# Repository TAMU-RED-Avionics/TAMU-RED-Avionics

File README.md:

# TAMU RED Avionics and Controls

This repository is home to the code and documentation for the Avionics and Controls subteam of the Texas A&M University Rocket Engine Design (<a href="https://www.tamured.space/">TAMU RED</a>) team.

## Organization

This repository is organized at the highest level by campaign. The current testing campaign is Elysium and all current code-related projects are found within. All previous campaigns are located within the Archive directory.

This repository is managed by <a href="https://github.com/Jacob-Hocevar">Jacob Hocevar</a>.

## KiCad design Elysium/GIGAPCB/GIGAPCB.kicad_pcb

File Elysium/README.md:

# Elysium
## Elysium GUI
The Elysium Graphical User Interface is the primary way that the system is controlled. It handels the inputs of the operator, automated control sequences, as well as the live display, graphing, and storage of data. It is programmed in C++ with Qt. For information on how to run and recompile (as needed), see the README.md in that directory.

## Real_Teensy
This directory contains the sketch(es) used by the Teensy to interpret the signals from the GUI, directly send the signals to actuate the valves, and read/transmit data from the sensors. Additionally, the system will handle an abort if there is a communications failure.

## Virtual_Teensy
This directory contains the code for a simulated version of the Teensy which is used to test the GUI. It recognizes and prints out any commands it recieves, and allows a user to control the data that it outputs to the GUI. For information on how to run and recompile (as needed), see the README.md in that directory.

Additionally, it will be configured to connect to another real Teensy to allow for Hardware In-the-Loop (HIL) testing.

## Data Formatting
For Elysium, all data will be transferred in `key:value` pairs. These pairs can be chained together in a comma separated string `"key1:val1,key2:val2,key3:val3\r\n"`, which terminates the carriage return (`'\r'`) and newline (`'\n'`) characters (the standard ending protocol for serial communication).The three goals are standardization, ease of maintainence/extension, and redundancy.

Standardization is both across programs and across subteams. We shall use the IDs of Sensors and Valves from the cross-team P&ID as the `key` terms, and the relevant data as the `value` terms. This will eliminate confusion between groups that were experienced in the WTS campaign, when one team was using `P1` and `P2`, and the other was using `PA` and `PB`.

This makes maintainence easier because it allows sensors and valves to be universally configured with a single, critical value. Similarly, if more valves or sensors are added, they can be added to the system with the same, single value.

This allows for some redundancy in the data transmission. If one value or part of a value fails to send correctly, the rest of the data in that batch (because of the keys), can still be readily and accurately identified by the receiver.

### Comparison to Older Design
Compare to the simpler system used during the WTS campaign: Comma separated values where the position dictates which property it corresponds to. First, the order of the properties had to be explicitly coordinated between the Teensy group and the GUI group and was not in reference to an existing, agreed upon document (such as the P&ID). Second, if a new sensor was added, both sides had to again determine where in the sequence to put the new value and manually hard-code it. Finally, if one value fails to send, all the following values (in that batch) are shifted and thus misread by the system.

### Example
Suppose the P&ID has three Pressure Transduces (P1-P3), two Thermocouples (T1 and T2) and one accelerometer (A1), which reads accelerations in three directions. The Teensy also outputs the local time with key `t`. Thus, it should output something like:

`"t:6545450000,P1:685.5422001,P2:14.78512405,P3:500.12124541,T1:7.2301502,T2:312.128575954,A1x:0.784213850,A1y:0.34517850652,A1z:2.0006781249\r\n"`

The order of the pairs does not matter, so something like the following is also acceptable, though less readable for debugging:

`"P3:500.12124541,A1x:0.784213850,P1:685.5422001,T2:312.128575954,A1z:2.0006781249,P2:14.78512405,T1:7.2301502,t:6545450000,A1y:0.34517850652\r\n"`

### Valve Example
For the valves, the solution is nearly identical, except that each command is always sent on its own line (no comma separated strings). Additionally, the value `0` always denotes a closed valve or close operation, and the value `1` always denotes an open valve or operation. For any extra electrical components (such as the ignition system), `0` will correspond to no power and `1` will correspond to providing power.

Consider a system with four normally closed solenoid valves (NCS1-NCS4) and two linearly-actuated ball valves (LA-BV 1 and LA-BV 2), and an igniter (IG1).

The signals to close all solenoids, open all ball valves and power igniter #1 would be given by:

`"NCS1:0\r\n"`
`"NCS2:0\r\n"`
`"NCS3:0\r\n"`
`"NCS4:0\r\n"`
`"LA-BV 1:1\r\n"`
`"LA-BV 2:1\r\n"`
`"IG1:1\r\n"`

Spaces in the IDs do not affect anything in either system. Again, these could be given in any order.

## Known Issues
There are a couple issues which have evaded all attempts to remove, but have simple methods to circumvent.

### GUI Freezes when connecting to Teensy
Identify: This typically results in the GUI freezing for several seconds, then expanding to full size, but not detecting any data inbound. It also will freeze upon shutdown or disconnect.

Cause: The connection to the Teensy is really sensitive with repeated connections and disconnections, especially with the WSL forwarding.

Solution: Unplug/replug the Teensy, and immediately attach it to WSL and attempt the connection again.<br>
A similar fix is to detach from WSL, and open the serial monitor in the Arduino IDE. Try opening and closing the serial monitor menu, and it should alternate between correct functionality, and a blank screen. When it is on a blank screen, close it, attach to WSL and attempt the connection again.

### GUI Connects, but the Teensy stays in the aborted state
Identify: GUI immediately "connects", but all data fields remain blank and the terminal is filled with `Not enough data: Aborted` and `Not enough data: New Input= nop`.

Cause: The connection to the Teensy is really sensitive and the first data sent over the connection often is lost/corrupted (buffer overriden?). This only occurs the first time after the Teensy is restarted.

Solution: Close the GUI and relaunch it. Not totally sure why, but it only ever happens the first time.

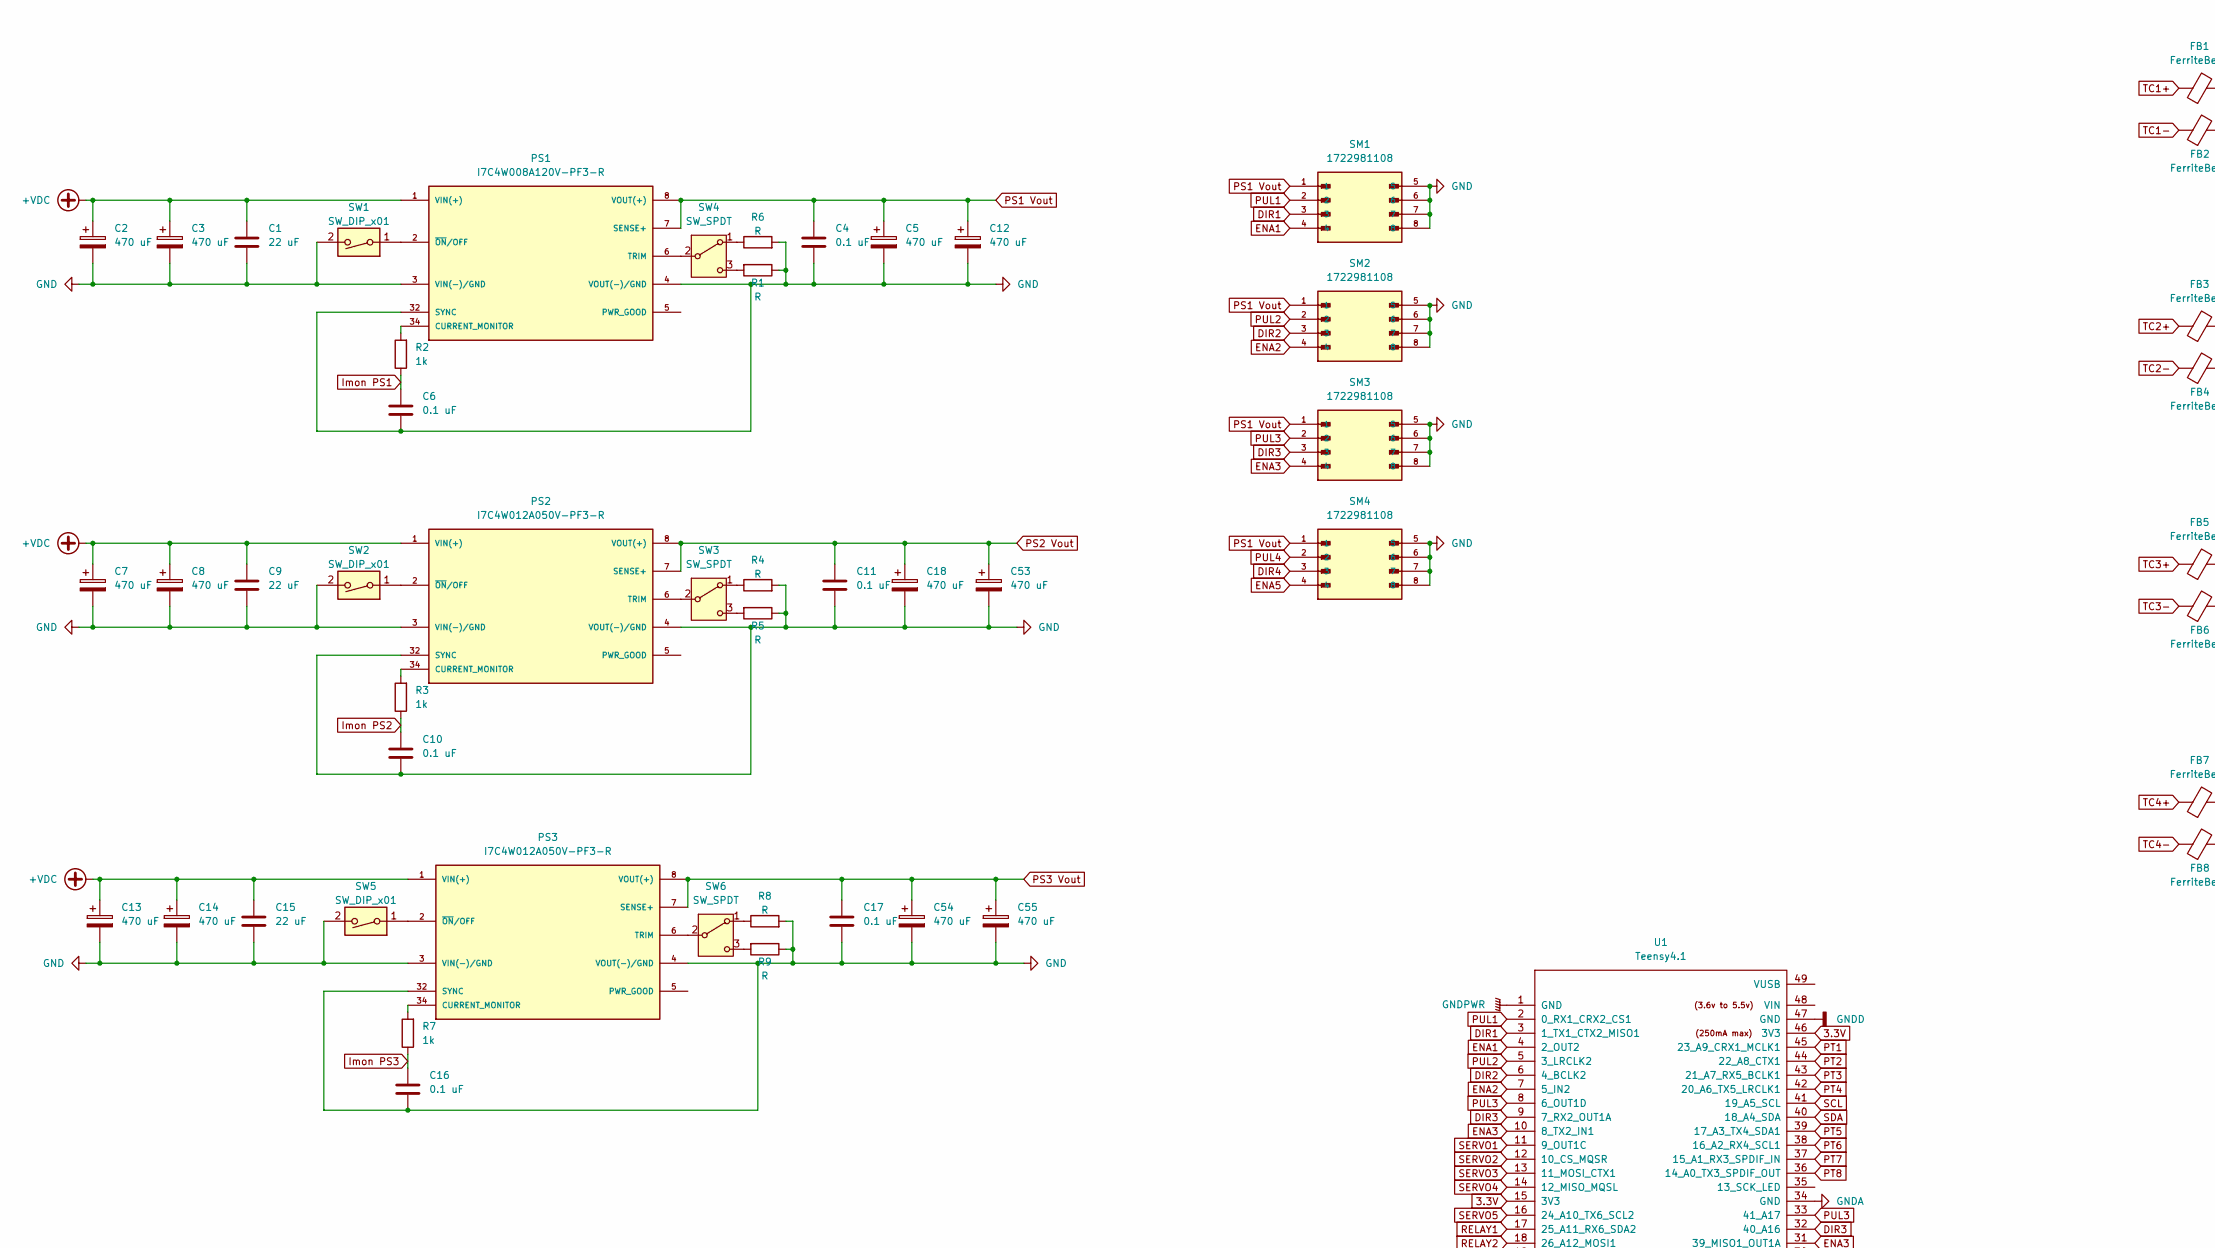
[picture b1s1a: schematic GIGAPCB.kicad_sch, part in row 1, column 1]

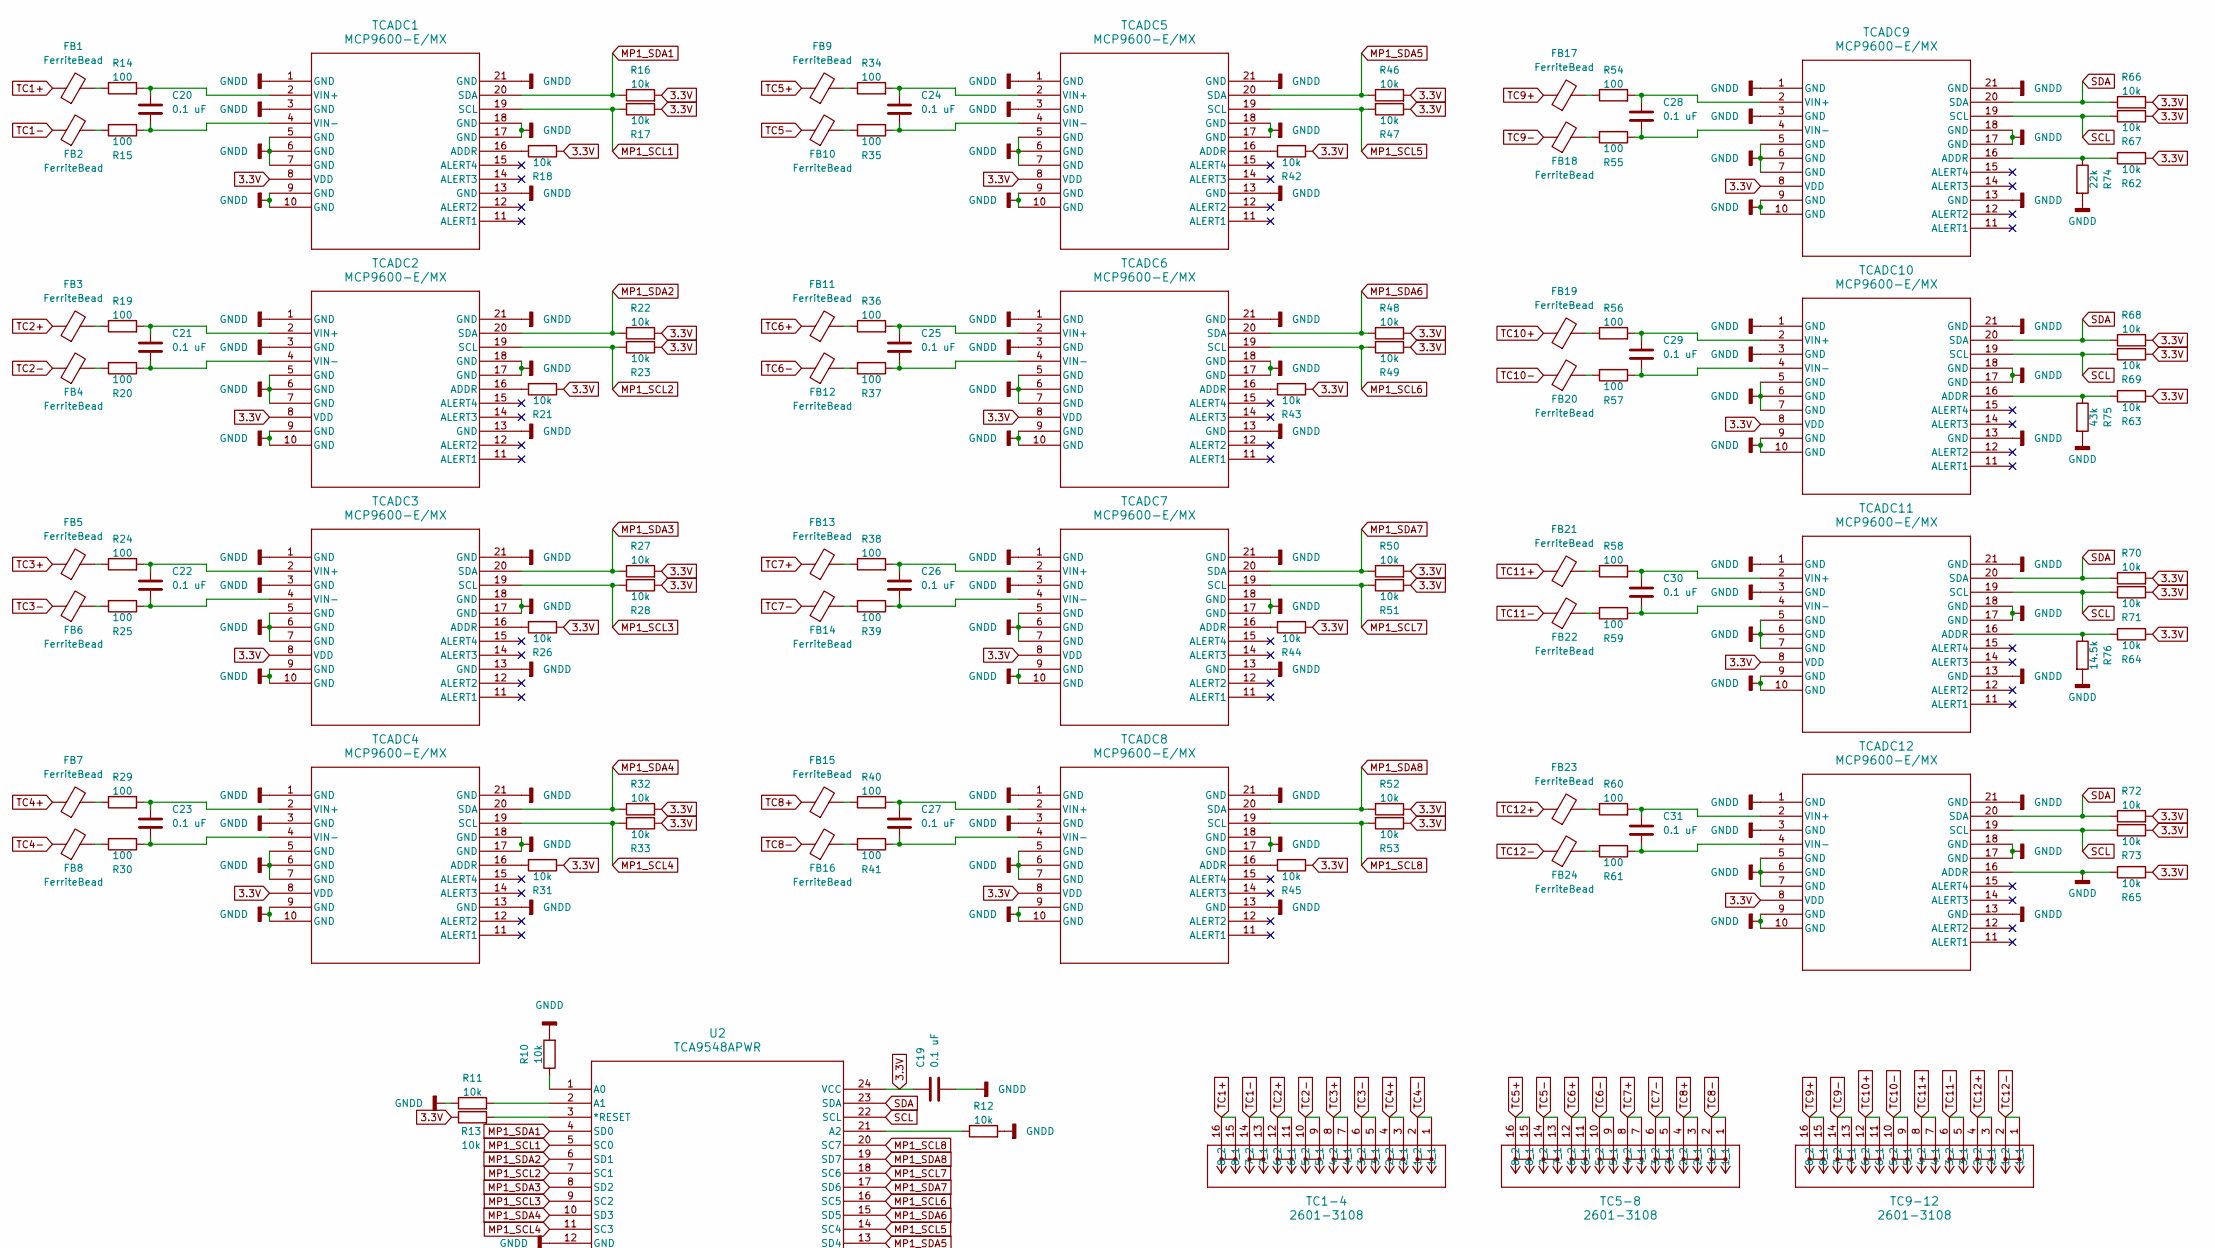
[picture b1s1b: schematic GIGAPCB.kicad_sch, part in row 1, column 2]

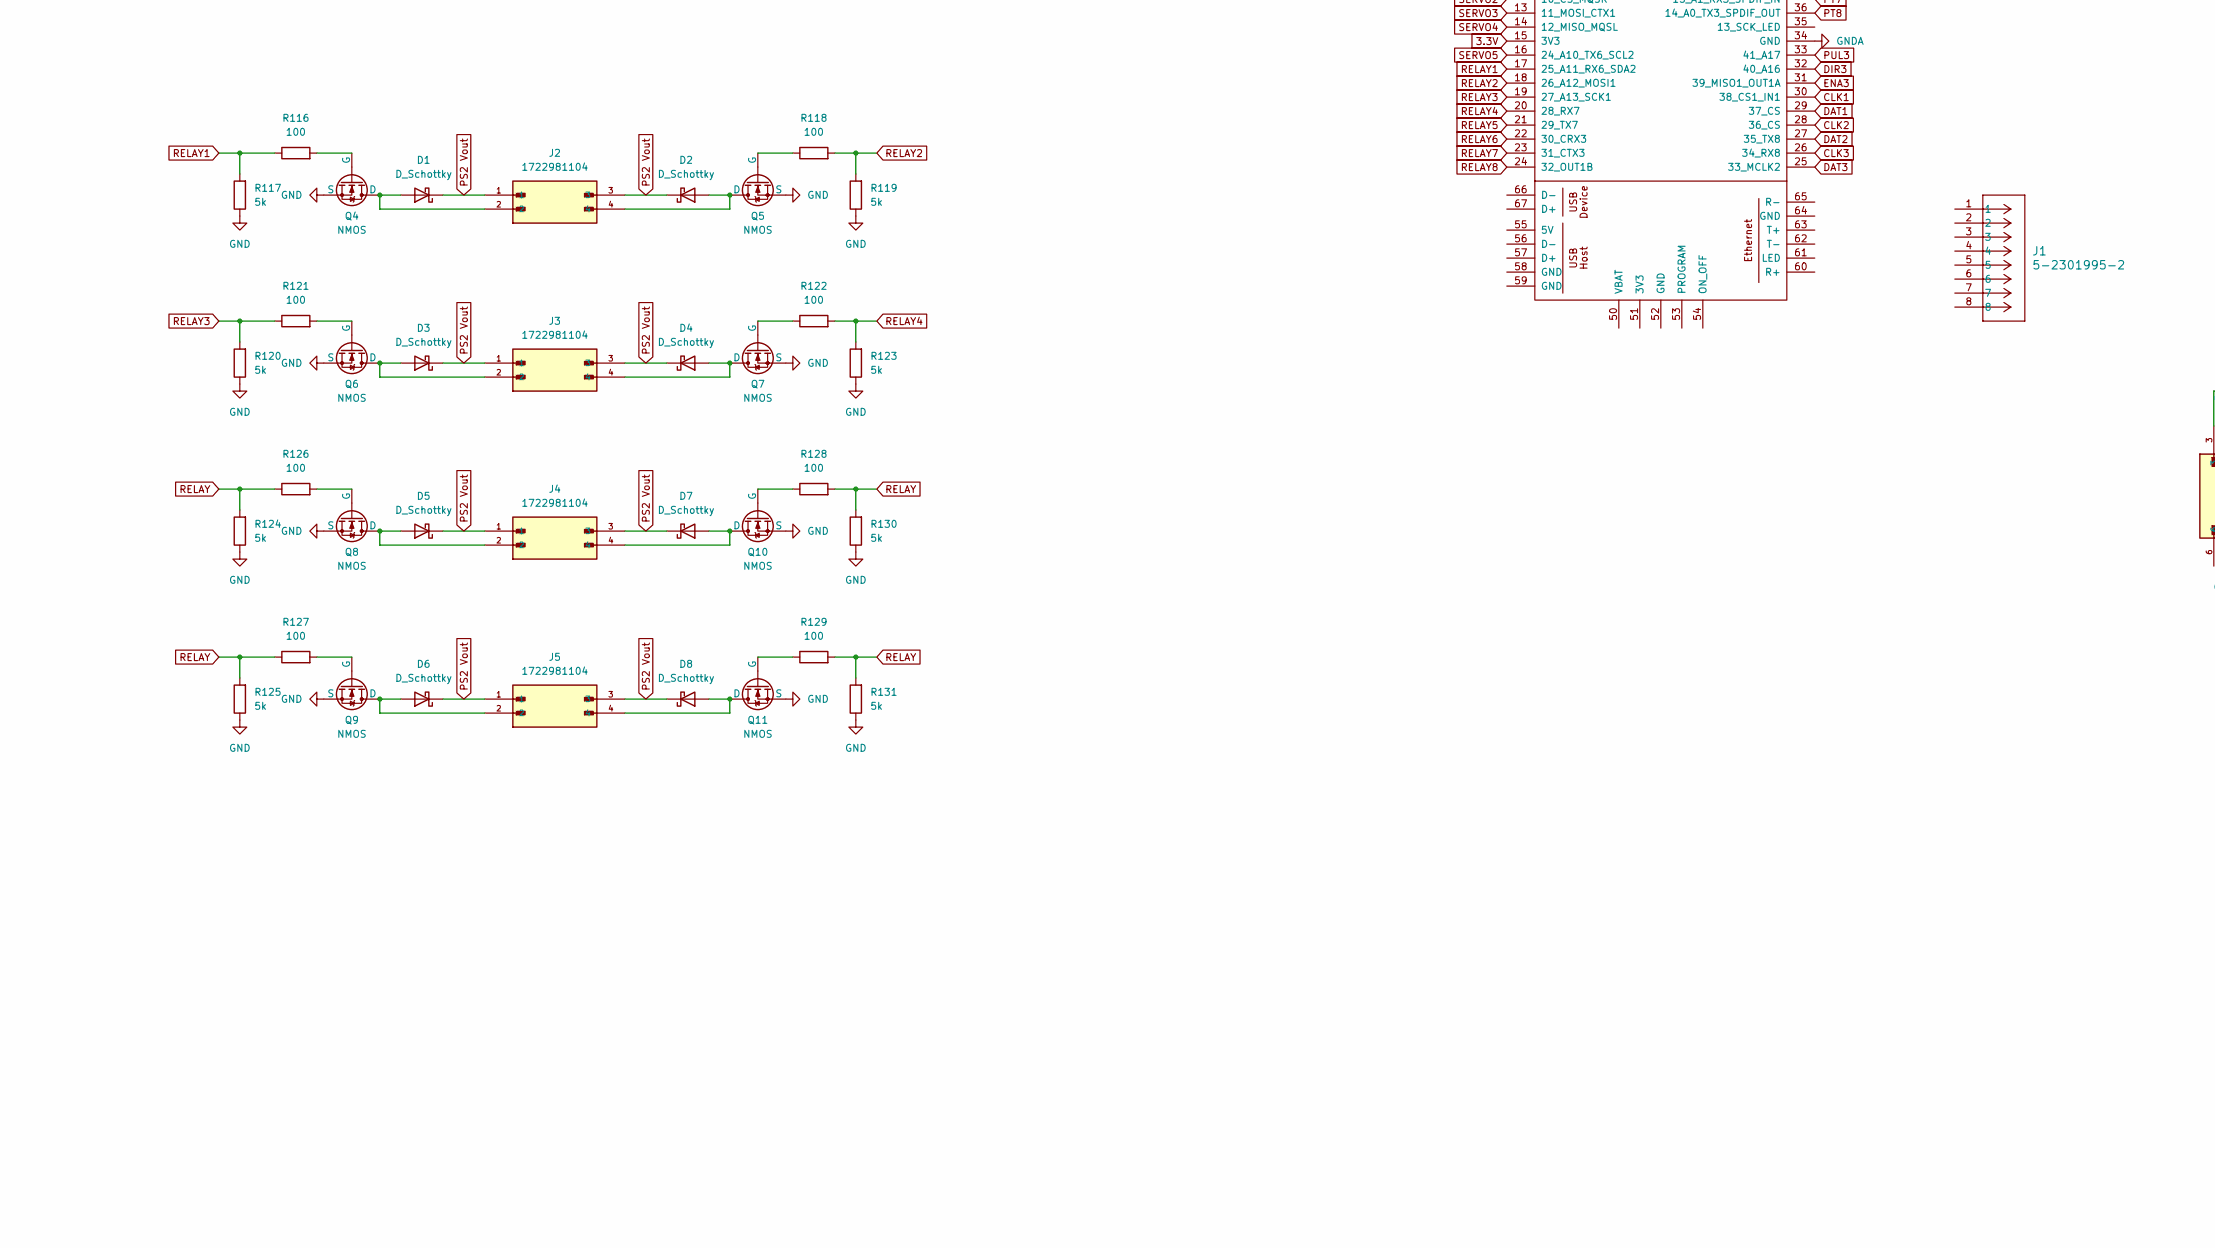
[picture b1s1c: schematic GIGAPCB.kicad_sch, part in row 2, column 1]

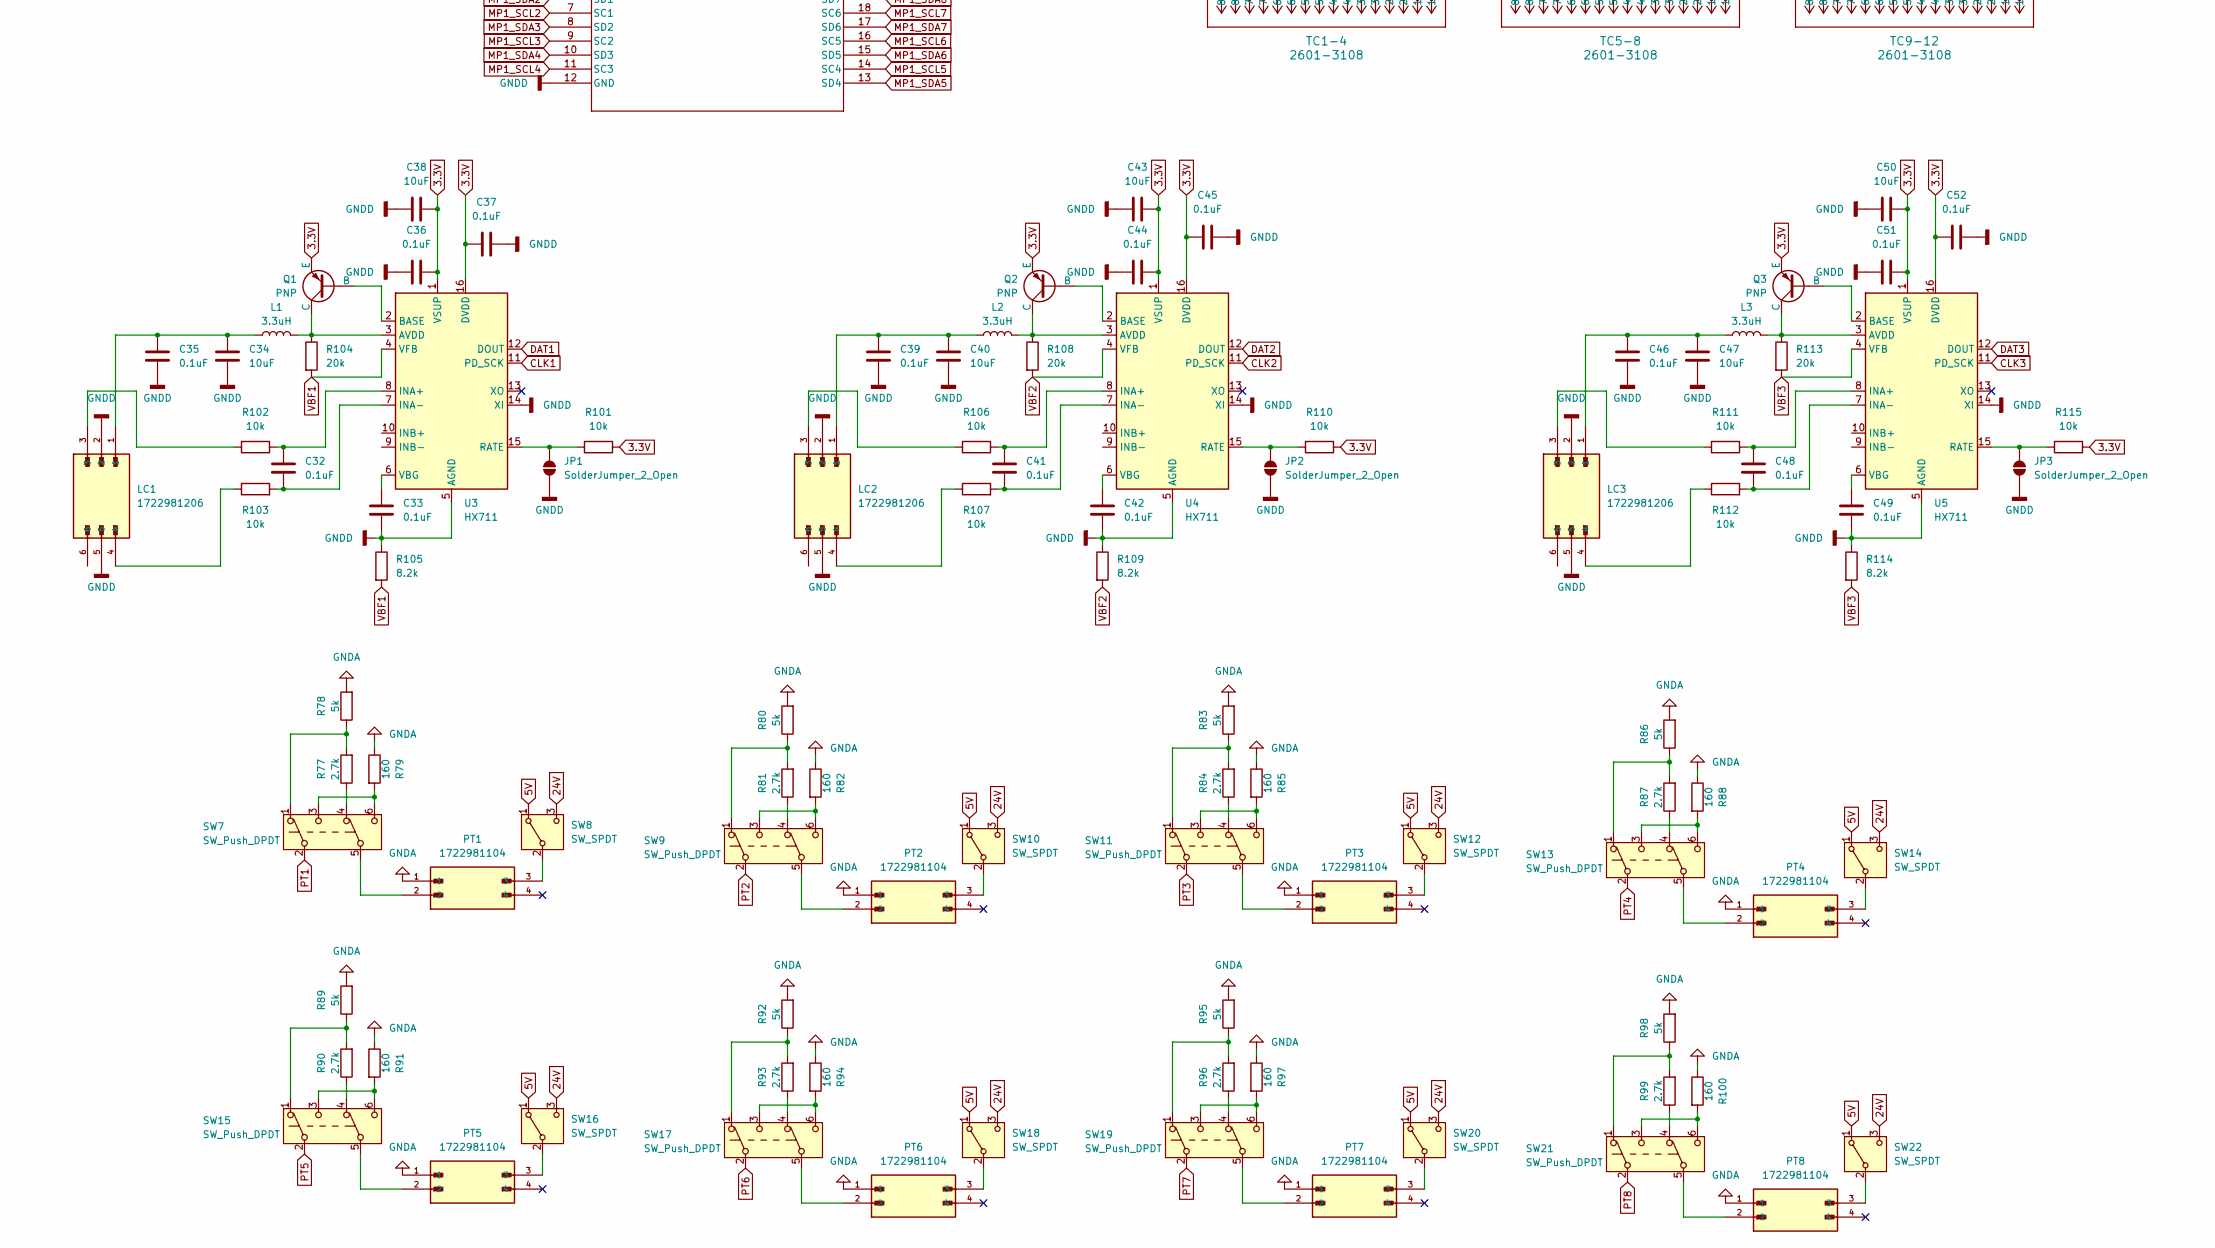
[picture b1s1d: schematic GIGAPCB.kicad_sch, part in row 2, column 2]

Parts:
C1, C9, C15: 22 uF; C_KRM55WR72A226MH01L
C2, C3, C5, C7, C8, C12, C13, C14, C18, C53, C54, C55: 470 uF; CP_EGPA101ELL471ML35S
C4, C6, C10, C11, C16, C17, C19, C20, C21, C22, C23, C24, C25, C26, C27, C28, C29, C30, C31: 0.1 uF; C_0805_2012Metric
C32, C33, C35, C36, C37, C39, C41, C42, C44, C45, C46, C48, C49, C51, C52: 0.1uF; C_0805_2012Metric
C34, C38, C40, C43, C47, C50: 10uF; C_1206_3216Metric
D1, D2, D3, D4, D5, D6, D7, D8: D_Schottky; D_PDS760_13-M
FB1, FB2, FB3, FB4, FB5, FB6, FB7, FB8, FB9, FB10, FB11, FB12, FB13, FB14, FB15, FB16, FB17, FB18, FB19, FB20, FB21, FB22, FB23, FB24: FerriteBead; R_0805_2012Metric
J1: 5-2301995-2; RJ25_Wayconn_MJEA-660X1_Horizontal
J2, J3, J4, J5: 1722981104; CONN_1722981104; PARTREV C1
JP1, JP2, JP3: SolderJumper_2_Open; SolderJumper-2_P1.3mm_Bridged2Bar_Pad1.0x1.5mm
L1, L2, L3: 3.3uH; C_0805_2012Metric
LC1, LC2, LC3: 1722981206; CONN_1722981106; PARTREV C1
PS1: I7C4W008A120V-PF3-R; DCC_I7C4W012A050V_PF3_R; PARTREV V5
PS2, PS3: I7C4W012A050V-PF3-R; DCC_I7C4W012A050V_PF3_R; PARTREV V5
PT1, PT2, PT3, PT4, PT5, PT6, PT7, PT8: 1722981104; CONN_1722981104; PARTREV C1
Q1: PNP; PinSocket_1x03_P2.54mm_Vertical
Q2, Q3: PNP
Q4, Q5, Q6, Q7, Q8, Q9, Q10, Q11: NMOS; MOSFET_CSD17306Q5A
R1, R4, R5, R6, R8, R9: R
R2, R3, R7: 1k
R10, R11, R12, R13, R16, R17, R18, R21, R22, R23, R26, R27, R28, R31, R32, R33, R42, R43, R44, R45, R46, R47, R48, R49, R50, R51, R52, R53, R62, R63, R64, R65, R66, R67, R68, R69, R70, R71, R72, R73, R101, R102, R103, R106, R107, R110, R111, R112, R115: 10k; R_0805_2012Metric
R14, R15, R19, R20, R24, R25, R29, R30, R34, R35, R36, R37, R38, R39, R40, R41, R54, R55, R56, R57, R58, R59, R60, R61, R116, R118, R121, R122, R126, R127, R128, R129: 100; R_0805_2012Metric
R74: 22k; R_0805_2012Metric
R75: 43k; R_0805_2012Metric
R76: 14.5k; R_0805_2012Metric
R77, R81, R84, R87, R90, R93, R96, R99: 2.7k; R_1206_3216Metric
R78, R80, R83, R86, R89, R92, R95, R98, R117, R119, R120, R123, R124, R125, R130, R131: 5k; R_1206_3216Metric
R79, R82, R85, R88, R91, R94, R97, R100: 160; R_1206_3216Metric
R104, R108, R113: 20k; R_0805_2012Metric
R105, R109, R114: 8.2k; R_0805_2012Metric
SM1, SM2, SM3, SM4: 1722981108; CONN_1722981108; PARTREV C1; DigiKey_Part_Number WM11582-ND
SW1, SW2, SW5: SW_DIP_x01
SW3, SW4, SW6, SW8, SW10, SW12, SW14, SW16, SW18, SW20, SW22: SW_SPDT; PinSocket_1x03_P2.54mm_Vertical
SW7, SW9, SW11, SW13, SW15, SW17, SW19, SW21: SW_Push_DPDT
TC1-4, TC5-8, TC9-12: 2601-3108; CONN_2601_3108
TCADC1, TCADC2, TCADC3, TCADC4, TCADC5, TCADC6, TCADC7, TCADC8, TCADC9, TCADC10, TCADC11, TCADC12: MCP9600-E/MX; IC_MCP9600-EMX-M
U1: Teensy4.1; Teensy41
U2: TCA9548APWR; IC_TCA9548APWR-M
U3, U4, U5: HX711; SOP-16_3.9x9.9mm_P1.27mm

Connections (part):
3.3V: C19.1, C36.2, C37.1, C38.2, C43.2, C44.2, C45.1, C50.2, C51.2, C52.1, Q1.3 (E), Q2.3 (E), Q3.3 (E), R13.1, R16.2, R17.1, R18.1, R21.1, R22.2, R23.1, R26.1, R27.2, R28.1, R31.1, R32.2, R33.1, R42.1, R43.1, R44.1, R45.1, R46.2, R47.1, R48.2, R49.1, R50.2, R51.1, R52.2, R53.1, R62.1, R63.1, R64.1, R65.1, R66.2, R67.1, R68.2, R69.1, R70.2, R71.1, R72.2, R73.1, R101.1, R110.1, R115.1, TCADC1.8 (VDD), TCADC2.8 (VDD), TCADC3.8 (VDD), TCADC4.8 (VDD), TCADC5.8 (VDD), TCADC6.8 (VDD), TCADC7.8 (VDD), TCADC8.8 (VDD), TCADC9.8 (VDD), TCADC10.8 (VDD), TCADC11.8 (VDD), TCADC12.8 (VDD), U1.15 (3V3), U1.46 (3V3), U2.24 (VCC), U3.1 (VSUP), U3.16 (DVDD), U4.1 (VSUP), U4.16 (DVDD), U5.1 (VSUP), U5.16 (DVDD)
5V: SW8.1 (A), SW10.1 (A), SW12.1 (A), SW14.1 (A), SW16.1 (A), SW18.1 (A), SW20.1 (A), SW22.1 (A)
24V: SW8.3 (C), SW10.3 (C), SW12.3 (C), SW14.3 (C), SW16.3 (C), SW18.3 (C), SW20.3 (C), SW22.3 (C)
+VDC: C1.1, C2.1, C3.1, C7.1, C8.1, C9.1, C13.1, C14.1, C15.1, PS1.1 (VIN(+)), PS2.1 (VIN(+)), PS3.1 (VIN(+))
CLK1: U1.30 (38_CS1_IN1), U3.11 (PD_SCK)
CLK2: U1.28 (36_CS), U4.11 (PD_SCK)
CLK3: U1.26 (34_RX8), U5.11 (PD_SCK)
DAT1: U1.29 (37_CS), U3.12 (DOUT)
DAT2: U1.27 (35_TX8), U4.12 (DOUT)
DAT3: U1.25 (33_MCLK2), U5.12 (DOUT)
DIR1: SM1.3, U1.3 (1_TX1_CTX2_MISO1)
DIR2: SM2.3, U1.6 (4_BCLK2)
DIR3: SM3.3, U1.9 (7_RX2_OUT1A), U1.32 (40_A16)
DIR4: SM4.3
ENA1: SM1.4, U1.4 (2_OUT2)
ENA2: SM2.4, U1.7 (5_IN2)
ENA3: SM3.4, U1.10 (8_TX2_IN1), U1.31 (39_MISO1_OUT1A)
ENA5: SM4.4
GND: C1.2, C2.2, C3.2, C4.2, C5.2, C6.2, C7.2, C8.2, C9.2, C10.2, C11.2, C12.2, C13.2, C14.2, C15.2, C16.2, C17.2, C18.2, C53.2, C54.2, C55.2, PS1.3 (VIN(-)/GND), PS1.4 (VOUT(-)/GND), PS1.32 (SYNC), PS2.3 (VIN(-)/GND), PS2.4 (VOUT(-)/GND), PS2.32 (SYNC), PS3.3 (VIN(-)/GND), PS3.4 (VOUT(-)/GND), PS3.32 (SYNC), Q4.3 (S), Q5.3 (S), Q6.3 (S), Q7.3 (S), Q8.3 (S), Q9.3 (S), Q10.3 (S), Q11.3 (S), R1.1, R4.2, R5.1, R6.2, R8.2, R9.1, R117.1, R119.1, R120.1, R123.1, R124.1, R125.1, R130.1, R131.1, SM1.5, SM1.6, SM1.7, SM1.8, SM2.5, SM2.6, SM2.7, SM2.8, SM3.5, SM3.6, SM3.7, SM3.8, SM4.5, SM4.6, SM4.7, SM4.8, SW1.2, SW2.2, SW5.2
GNDA: PT1.1, PT2.1, PT3.1, PT4.1, PT5.1, PT6.1, PT7.1, PT8.1, R78.2, R79.1, R80.2, R82.1, R83.2, R85.1, R86.2, R88.1, R89.2, R91.1, R92.2, R94.1, R95.2, R97.1, R98.2, R100.1, U1.34 (GND)
GNDD: C19.2, C33.2, C34.2, C35.2, C36.1, C37.2, C38.1, C39.2, C40.2, C42.2, C43.1, C44.1, C45.2, C46.2, C47.2, C49.2, C50.1, C51.1, C52.2, JP1.1 (A), JP2.1 (A), JP3.1 (A), LC1.2, LC1.5, LC2.2, LC2.5, LC3.2, LC3.5, R10.2, R11.1, R12.2, R65.2, R74.2, R75.2, R76.2, R105.1, R109.1, R114.1, TCADC1.1 (GND), TCADC1.3 (GND), TCADC1.5 (GND), TCADC1.6 (GND), TCADC1.7 (GND), TCADC1.9 (GND), TCADC1.10 (GND), TCADC1.13 (GND), TCADC1.17 (GND), TCADC1.18 (GND), TCADC1.21 (GND), TCADC2.1 (GND), TCADC2.3 (GND), TCADC2.5 (GND), TCADC2.6 (GND), TCADC2.7 (GND), TCADC2.9 (GND), TCADC2.10 (GND), TCADC2.13 (GND), TCADC2.17 (GND), TCADC2.18 (GND), TCADC2.21 (GND), TCADC3.1 (GND), TCADC3.3 (GND), TCADC3.5 (GND), TCADC3.6 (GND), TCADC3.7 (GND), TCADC3.9 (GND), TCADC3.10 (GND), TCADC3.13 (GND), TCADC3.17 (GND), TCADC3.18 (GND), TCADC3.21 (GND), TCADC4.1 (GND), TCADC4.3 (GND), TCADC4.5 (GND), TCADC4.6 (GND), TCADC4.7 (GND), TCADC4.9 (GND), TCADC4.10 (GND), TCADC4.13 (GND), TCADC4.17 (GND), TCADC4.18 (GND)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
GNDPWR: U1.1 (GND)
Imon PS1: C6.1, R2.1
Imon PS2: C10.1, R3.1
Imon PS3: C16.1, R7.1
MP1_SCL1: R17.2, TCADC1.19 (SCL), U2.5 (SC0)
MP1_SCL2: R23.2, TCADC2.19 (SCL), U2.7 (SC1)
MP1_SCL3: R28.2, TCADC3.19 (SCL), U2.9 (SC2)
MP1_SCL4: R33.2, TCADC4.19 (SCL), U2.11 (SC3)
MP1_SCL5: R47.2, TCADC5.19 (SCL), U2.14 (SC4)
MP1_SCL6: R49.2, TCADC6.19 (SCL), U2.16 (SC5)
MP1_SCL7: R51.2, TCADC7.19 (SCL), U2.18 (SC6)
MP1_SCL8: R53.2, TCADC8.19 (SCL), U2.20 (SC7)
MP1_SDA1: R16.1, TCADC1.20 (SDA), U2.4 (SD0)
MP1_SDA2: R22.1, TCADC2.20 (SDA), U2.6 (SD1)
MP1_SDA3: R27.1, TCADC3.20 (SDA), U2.8 (SD2)
MP1_SDA4: R32.1, TCADC4.20 (SDA), U2.10 (SD3)
MP1_SDA5: R46.1, TCADC5.20 (SDA), U2.13 (SD4)
MP1_SDA6: R48.1, TCADC6.20 (SDA), U2.15 (SD5)
MP1_SDA7: R50.1, TCADC7.20 (SDA), U2.17 (SD6)
MP1_SDA8: R52.1, TCADC8.20 (SDA), U2.19 (SD7)
unnamed: C34.1, C35.1, L1.1, LC1.1
unnamed: C39.1, C40.1, L2.1, LC2.1
unnamed: C46.1, C47.1, L3.1, LC3.1
unnamed: D1.2 (A), J2.2, Q4.1 (D)
unnamed: D2.2 (A), J2.4, Q5.1 (D)
unnamed: D3.2 (A), J3.2, Q6.1 (D)
unnamed: D4.2 (A), J3.4, Q7.1 (D)
unnamed: D5.2 (A), J4.2, Q8.1 (D)
unnamed: D6.2 (A), J5.2, Q9.1 (D)
unnamed: D7.2 (A), J4.4, Q10.1 (D)
unnamed: D8.2 (A), J5.4, Q11.1 (D)
unnamed: FB1.2, R14.1
unnamed: FB2.2, R15.2
unnamed: FB3.2, R19.1
unnamed: FB4.2, R20.2
unnamed: FB5.2, R24.1
unnamed: FB6.2, R25.2
unnamed: FB7.2, R29.1
unnamed: FB8.2, R30.2
unnamed: FB9.2, R34.1
unnamed: FB10.2, R35.2
unnamed: FB11.2, R36.1
unnamed: FB12.2, R37.2
unnamed: FB13.2, R38.1
unnamed: FB14.2, R39.2
unnamed: FB15.2, R40.1
unnamed: FB16.2, R41.2
unnamed: FB17.2, R54.1
unnamed: FB18.2, R55.2
unnamed: FB19.2, R56.1
unnamed: FB20.2, R57.2
unnamed: FB21.2, R58.1
unnamed: FB22.2, R59.2
unnamed: FB23.2, R60.1
unnamed: FB24.2, R61.2
unnamed: JP1.2 (B), R101.2, U3.15 (RATE)
unnamed: JP2.2 (B), R110.2, U4.15 (RATE)
unnamed: JP3.2 (B), R115.2, U5.15 (RATE)
unnamed: LC1.3, R102.2
unnamed: LC1.4, R103.1
unnamed: LC2.3, R106.2
unnamed: LC2.4, R107.1
unnamed: LC3.3, R111.2
unnamed: LC3.4, R112.1
unnamed: PS1.34 (CURRENT_MONITOR), R2.2
unnamed: PS1.6 (TRIM), SW4.2 (B)
unnamed: PS1.2 (~ON/OFF), SW1.1
unnamed: PS2.34 (CURRENT_MONITOR), R3.2
unnamed: PS2.6 (TRIM), SW3.2 (B)
unnamed: PS2.2 (~ON/OFF), SW2.1
unnamed: PS3.34 (CURRENT_MONITOR), R7.2
unnamed: PS3.6 (TRIM), SW6.2 (B)
unnamed: PS3.2 (~ON/OFF), SW5.1
unnamed: PT1.2, SW7.5 (B)
unnamed: PT2.2, SW9.5 (B)
unnamed: PT3.2, SW11.5 (B)
unnamed: PT4.2, SW13.5 (B)
unnamed: PT5.2, SW15.5 (B)
unnamed: PT6.2, SW17.5 (B)
unnamed: PT7.2, SW19.5 (B)
unnamed: PT8.2, SW21.5 (B)
unnamed: Q1.2 (B), U3.2 (BASE)
unnamed: L1.2, Q1.1 (C), R104.1, U3.3 (AVDD)
unnamed: Q2.2 (B), U4.2 (BASE)
unnamed: L2.2, Q2.1 (C), R108.1, U4.3 (AVDD)
unnamed: Q3.2 (B), U5.2 (BASE)
unnamed: L3.2, Q3.1 (C), R113.1, U5.3 (AVDD)
unnamed: Q4.2 (G), R116.2
unnamed: Q5.2 (G), R118.1
unnamed: Q6.2 (G), R121.2
unnamed: Q7.2 (G), R122.1
unnamed: Q8.2 (G), R126.2
unnamed: Q9.2 (G), R127.2
unnamed: Q10.2 (G), R128.1
unnamed: Q11.2 (G), R129.1
unnamed: R77.1, SW7.4 (A)
unnamed: R77.2, R78.1, SW7.1 (A)
unnamed: R79.2, SW7.3 (C), SW7.6 (C)
unnamed: R80.1, R81.2, SW9.1 (A)
unnamed: R81.1, SW9.4 (A)
unnamed: R82.2, SW9.3 (C), SW9.6 (C)
unnamed: R83.1, R84.2, SW11.1 (A)
unnamed: R84.1, SW11.4 (A)
unnamed: R85.2, SW11.3 (C), SW11.6 (C)
unnamed: R86.1, R87.2, SW13.1 (A)
unnamed: R87.1, SW13.4 (A)
unnamed: R88.2, SW13.3 (C), SW13.6 (C)
unnamed: R89.1, R90.2, SW15.1 (A)
unnamed: R90.1, SW15.4 (A)
unnamed: R91.2, SW15.3 (C), SW15.6 (C)
unnamed: R92.1, R93.2, SW17.1 (A)
unnamed: R93.1, SW17.4 (A)
unnamed: R94.2, SW17.3 (C), SW17.6 (C)
unnamed: R95.1, R96.2, SW19.1 (A)
unnamed: R96.1, SW19.4 (A)
unnamed: R97.2, SW19.3 (C), SW19.6 (C)
unnamed: R98.1, R99.2, SW21.1 (A)
unnamed: R99.1, SW21.4 (A)
unnamed: R100.2, SW21.3 (C), SW21.6 (C)
unnamed: R4.1, SW3.1 (A)
unnamed: R5.2, SW3.3 (C)
unnamed: R6.1, SW4.1 (A)
unnamed: R1.2, SW4.3 (C)
unnamed: R8.1, SW6.1 (A)
unnamed: R9.2, SW6.3 (C)
unnamed: PT1.3, SW8.2 (B)
unnamed: PT2.3, SW10.2 (B)
unnamed: PT3.3, SW12.2 (B)
unnamed: PT4.3, SW14.2 (B)
unnamed: PT5.3, SW16.2 (B)
unnamed: PT6.3, SW18.2 (B)
unnamed: PT7.3, SW20.2 (B)
unnamed: PT8.3, SW22.2 (B)
unnamed: R18.2, TCADC1.16 (ADDR)
unnamed: C20.1, R14.2, TCADC1.2 (VIN+)
unnamed: C20.2, R15.1, TCADC1.4 (VIN-)
unnamed: R21.2, TCADC2.16 (ADDR)
unnamed: C21.1, R19.2, TCADC2.2 (VIN+)
unnamed: C21.2, R20.1, TCADC2.4 (VIN-)
unnamed: R26.2, TCADC3.16 (ADDR)
unnamed: C22.1, R24.2, TCADC3.2 (VIN+)
unnamed: C22.2, R25.1, TCADC3.4 (VIN-)
unnamed: R31.2, TCADC4.16 (ADDR)
unnamed: C23.1, R29.2, TCADC4.2 (VIN+)
unnamed: C23.2, R30.1, TCADC4.4 (VIN-)
unnamed: R42.2, TCADC5.16 (ADDR)
unnamed: C24.1, R34.2, TCADC5.2 (VIN+)
unnamed: C24.2, R35.1, TCADC5.4 (VIN-)
unnamed: R43.2, TCADC6.16 (ADDR)
unnamed: C25.1, R36.2, TCADC6.2 (VIN+)
unnamed: C25.2, R37.1, TCADC6.4 (VIN-)
unnamed: R44.2, TCADC7.16 (ADDR)
unnamed: C26.1, R38.2, TCADC7.2 (VIN+)
unnamed: C26.2, R39.1, TCADC7.4 (VIN-)
unnamed: R45.2, TCADC8.16 (ADDR)
unnamed: C27.1, R40.2, TCADC8.2 (VIN+)
unnamed: C27.2, R41.1, TCADC8.4 (VIN-)
unnamed: R62.2, R74.1, TCADC9.16 (ADDR)
unnamed: C28.1, R54.2, TCADC9.2 (VIN+)
unnamed: C28.2, R55.1, TCADC9.4 (VIN-)
unnamed: R63.2, R75.1, TCADC10.16 (ADDR)
unnamed: C29.1, R56.2, TCADC10.2 (VIN+)
unnamed: C29.2, R57.1, TCADC10.4 (VIN-)
unnamed: R64.2, R76.1, TCADC11.16 (ADDR)
unnamed: C30.1, R58.2, TCADC11.2 (VIN+)
unnamed: C30.2, R59.1, TCADC11.4 (VIN-)
unnamed: C31.1, R60.2, TCADC12.2 (VIN+)
unnamed: C31.2, R61.1, TCADC12.4 (VIN-)
unnamed: R13.2, U2.3 (*RESET)
unnamed: R10.1, U2.1 (A0)
unnamed: R11.2, U2.2 (A1)
unnamed: R12.1, U2.21 (A2)
unnamed: C32.1, R102.1, U3.8 (INA+)
unnamed: C32.2, R103.2, U3.7 (INA-)
unnamed: C33.1, U3.6 (VBG)
unnamed: C41.1, R106.1, U4.8 (INA+)
unnamed: C41.2, R107.2, U4.7 (INA-)
unnamed: C42.1, U4.6 (VBG)
unnamed: C48.1, R111.1, U5.8 (INA+)
unnamed: C48.2, R112.2, U5.7 (INA-)
unnamed: C49.1, U5.6 (VBG)
PS1 Vout: C4.1, C5.1, C12.1, PS1.7 (SENSE+), PS1.8 (VOUT(+)), SM1.1, SM2.1, SM3.1, SM4.1
PS2 Vout: C11.1, C18.1, C53.1, D1.1 (K), D2.1 (K), D3.1 (K), D4.1 (K), D5.1 (K), D6.1 (K), D7.1 (K), D8.1 (K), J2.1, J2.3, J3.1, J3.3, J4.1, J4.3, J5.1, J5.3, PS2.7 (SENSE+), PS2.8 (VOUT(+))
PS3 Vout: C17.1, C54.1, C55.1, PS3.7 (SENSE+), PS3.8 (VOUT(+))
PT1: SW7.2 (B), U1.45 (23_A9_CRX1_MCLK1)
PT2: SW9.2 (B), U1.44 (22_A8_CTX1)
PT3: SW11.2 (B), U1.43 (21_A7_RX5_BCLK1)
PT4: SW13.2 (B), U1.42 (20_A6_TX5_LRCLK1)
PT5: SW15.2 (B), U1.39 (17_A3_TX4_SDA1)
PT6: SW17.2 (B), U1.38 (16_A2_RX4_SCL1)
PT7: SW19.2 (B), U1.37 (15_A1_RX3_SPDIF_IN)
PT8: SW21.2 (B), U1.36 (14_A0_TX3_SPDIF_OUT)
PUL1: SM1.2, U1.2 (0_RX1_CRX2_CS1)
PUL2: SM2.2, U1.5 (3_LRCLK2)
PUL3: SM3.2, U1.8 (6_OUT1D), U1.33 (41_A17)
PUL4: SM4.2
RELAY: R124.2, R125.2, R126.1, R127.1, R128.2, R129.2, R130.2, R131.2
RELAY1: R116.1, R117.2, U1.17 (25_A11_RX6_SDA2)
RELAY2: R118.2, R119.2, U1.18 (26_A12_MOSI1)
RELAY3: R120.2, R121.1, U1.19 (27_A13_SCK1)
RELAY4: R122.2, R123.2, U1.20 (28_RX7)
RELAY5: U1.21 (29_TX7)
RELAY6: U1.22 (30_CRX3)
RELAY7: U1.23 (31_CTX3)
RELAY8: U1.24 (32_OUT1B)
SCL: R67.2, R69.2, R71.2, R73.2, TCADC9.19 (SCL), TCADC10.19 (SCL), TCADC11.19 (SCL), TCADC12.19 (SCL), U1.41 (19_A5_SCL), U2.22 (SCL)
SDA: R66.1, R68.1, R70.1, R72.1, TCADC9.20 (SDA), TCADC10.20 (SDA), TCADC11.20 (SDA), TCADC12.20 (SDA), U1.40 (18_A4_SDA), U2.23 (SDA)
SERVO1: U1.11 (9_OUT1C)
SERVO2: U1.12 (10_CS_MQSR)
SERVO3: U1.13 (11_MOSI_CTX1)
SERVO4: U1.14 (12_MISO_MQSL)
SERVO5: U1.16 (24_A10_TX6_SCL2)
TC1+: FB1.1, TC1-4.15 (8_1), TC1-4.16 (8_2)
TC1-: FB2.1, TC1-4.13 (7_1), TC1-4.14 (7_2)
TC2+: FB3.1, TC1-4.11 (6_1), TC1-4.12 (6_2)
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
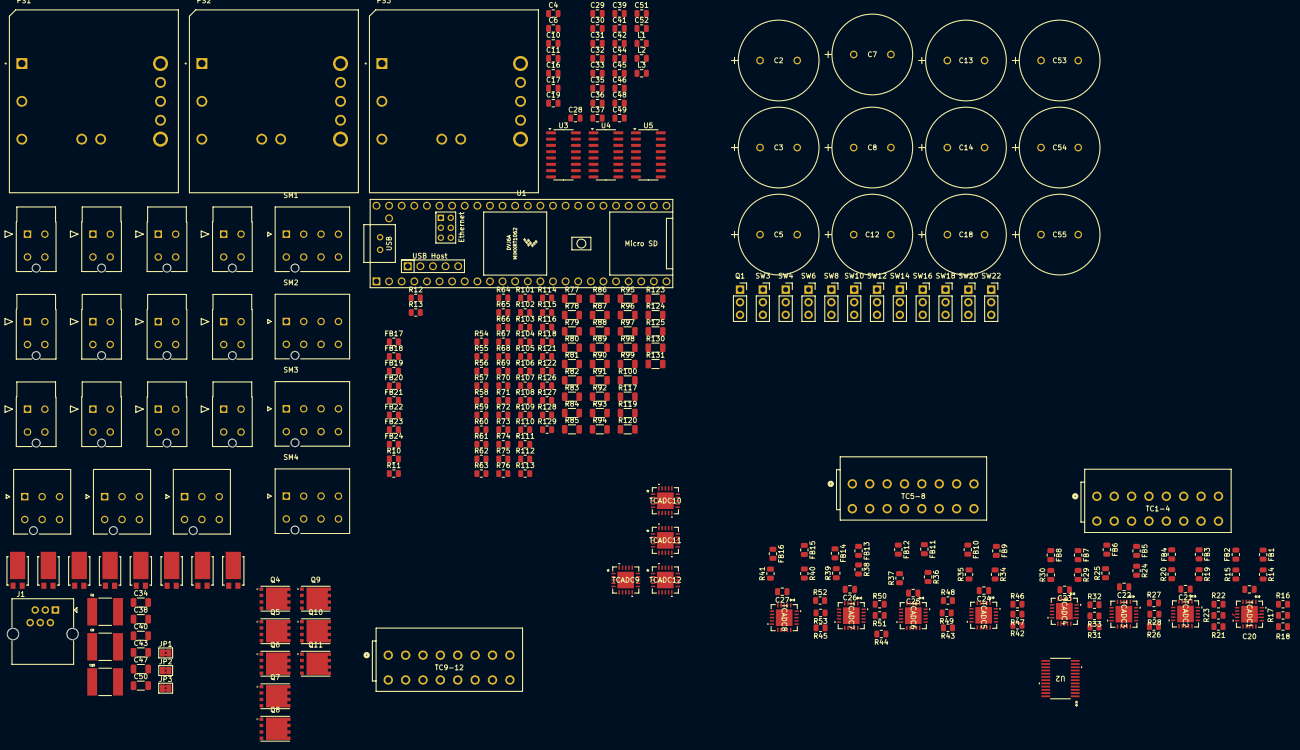
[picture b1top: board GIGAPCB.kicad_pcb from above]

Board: 4 copper layers, 278 parts (0 on the bottom side), 198 nets.

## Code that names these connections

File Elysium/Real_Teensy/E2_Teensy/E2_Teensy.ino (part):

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
const int BAUD = 115200;

// Relay line -> Teensy pin, traced from the daughter card PCB
// (Teensy_Daughtercard.kicad_pcb v2.5, J6 -> U1). Relays 5, 6 and 14 stop at J6: their
// pins now carry SPI1 to the AD5420, so those three lines are not driven by anything.
// The other 13 are routed on copper. Relay 16 is spare.
//   relay  1 = pin 31 (J6-11)    relay  9 = pin  9 (J6-7)
//   relay  2 = pin 30 (J6-36)    relay 10 = pin  8 (J6-32)
//   relay  3 = pin 29 (J6-10)    relay 11 = pin  7 (J6-6)
//   relay  4 = pin 28 (J6-35)    relay 12 = pin  5 (J6-5)
//   relay  5 = pin 27 (J6-9)     relay 13 = pin  3 (J6-4)
//   relay  6 = pin 26 (J6-34)    relay 14 = pin  1 (J6-3)
//   relay  7 = pin 24 (J6-33)    relay 15 = pin 21 (J6-1)
//   relay  8 = pin 25 (J6-8)     relay 16 = pin 20 (J6-2)
const int NCS1_PIN   = 8;    // relay 10
const int NCS2_PIN   = 7;    // relay 11
const int NCS3_PIN   = 5;    // relay 12
// NCS4 is a manual switch (no relay). NCS5 = FV-1201 (ID 0x04) is wired to relay 13.
const int NCS5_PIN   = 3;    // relay 13 (FV-1201)
// Pins 26/27 are SPI1 MOSI/SCK, which the AD5420 (Bray valve) needs, so PA-BV1 has no
// relay and PA-BV3 / NCS6 (ID 0x06) moved from relay 5 to relay 15.
const int PA_BV3_PIN = 21;   // relay 15 (J6-1)
const int PA_BV1_PIN = -1;   // was 26 (relay 6)
const int PA_BV2_PIN = 24;   // relay 7
const int PNEUMA_PIN = -1;   // was pin 3 (relay 13); relay 13 now drives NCS5 / FV-1201
// Relay 9 powers the Bray positioner card (AD5420 daughtercard input J9). Relay outputs are
// LOW-SIDE switches, so relay 9 (GIGAPCB J5: +12 V on pins 1/2, switched return on 3/4) drives
// the coil of a small 12 V relay whose contacts switch the +12 V to J9 pin 2 - the card's own
// ground stays tied to the Teensy ground. -1 = card is wired straight to the rail (always on).
const int BRAY_PWR_PIN = 9;    // relay 9 (J6-7)
const int BRAY_AUX_PIN = -1;  // relay 14 = pin 1, but pin 1 is the AD5420's SPI1 MISO - unassigned until that moves
const int FP_1201_PIN = 29;   // relay 3 - fuel pump FP-1201 (ID 0x12)
const int AP_1601_PIN = 28;   // relay 4 - air compressor AP-1601 (ID 0x13)
const int GV1_PIN    = 25;   // relay 8
const int GV2_PIN    = -1;
const int IGN1_PIN   = 31;   // relay 1
const int IGN2_PIN   = 30;   // relay 2
const int GIMBAL_PIN = -1;


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const float    PT_NO_SIGNAL_MA = 3.85f;

// ADS channel -> PT index (0-based; 0 = P1), traced from the PCB netlist:
//   J10 pins 1-4 = ch0-3  = PT6, PT0, PT7, PT1
//   J15 pins 1-4 = ch4-7  = PT8, PT2, PT9, PT3
//   J19 pins 1-4 = ch8-11 = PT10, PT4, PT11, PT5
// Confirmed on the bench: P2 = ch3, P6 = ch11, P8 = ch2.
const uint8_t PT_NUM_FOR_CH[12] = { 6, 0, 7, 1, 8, 2, 9, 3, 10, 4, 11, 5 };

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
int get_pin_from_valve_id(uint8_t id) {
    switch (id) {
        case 0x0A: return NCS1_PIN;   // NCS1 = relay 10
        case 0x0B: return NCS2_PIN;   // NCS2 = relay 11
        case 0x0C: return NCS3_PIN;   // NCS3 = relay 12
        case 0x04: return NCS5_PIN;   // NCS5 (FV-1201) is relay 13
        case 0x06: return PA_BV3_PIN;   // NCS6 = relay 15
        case 0x0D: return PNEUMA_PIN;   // Pneuma - unassigned (relay 13 went to NCS5)
        case 0x0E: return BRAY_AUX_PIN;  // relay 14, also follows the Bray valve
        case 0x10: return PA_BV1_PIN;   // was LA-BV1
        case 0x11: return PA_BV2_PIN;   // was LA-BV2
        case 0x12: return FP_1201_PIN;  // FP-1201 fuel pump = relay 3
        case 0x13: return AP_1601_PIN;  // AP-1601 air compressor = relay 4
        case 0x20: return GV1_PIN;
        case 0x21: return GV2_PIN;
        case 0x30: return IGN1_PIN;
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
